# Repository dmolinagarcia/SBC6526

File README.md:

# SBC6526

SBC6526 is a single board computer built around A 65c02 CPU. It has been designed with a very specific purpose, that has defined both its name and its specs. I've been working for some time already on a MOS6526 (The famous CIA used in Commodore Computers) replica using 74xx logic series ICs. Testing was done on a real C64, but soon this prove to be a very limiting factor. So I begin working on a small SBC, designed entirely around the 6526, that should allow me to run as many tests, with no limitations at all.

The initial set of requisites was

* Continuosly variable clock, from 1MHz to as far as possible, in order to push my replica to its limits
* Clock Frequency Display. Useful, and should look very cool.
* No input at all. Program the ROM (more on this later) and just run a suite of tests for the 6526.
* Basic output.. Something like a 20x4 Character LCD will do.
* Easy, quick, and on board ROM programming. I will be modifiying the code continuosly, so this is very important.
* Include a 6522. Why not!? It can also be useful for the tests
* Include a socket for a 6526. Compatibility with old NMOS 6526 is not needed, although it would be nice.
* Allow testing of all 6526 pins. Ports, serial, /FLAG interrupt, etc
* Independent reset for 6526.

SBCv1 came to life, fulfilling this requirements. Howeever, after using it for some time, it show some weakness. SBCv1 has a 6522 and a 6526. A 4x40 LCD is used as display, driven by the 6526. This causes the display to blank when running some tests, and sometimes, crashed the LCD into an unrecoverable state, that requires a complete power down. This along some layout issues, forced the next revision. 

## Memory Map

0000 - 7FFF RAM
8000 - 87FF I/O BANK 0 - FREE
8800 - 8FFF I/O BANK 1 - CIA1
9000 - 97FF I/O BANK 2 - VIA
9800 - 9FFF I/O BANK 3 - CIAEXT
A000 - A7FF I/O BANK 4
A800 - AFFF I/O BANK 5
B000 - B7FF I/O BANK 6
B800 - BFFF I/O BANK 7
C000 - FFFF RAM

# v2
Being my first attempt at creating a SBC, v1 had many flaws. There were some pull-up resistors missing, the PCB layout was a mess, the bootstrap code was... well... unreadable to be honest. Moreover, the CAD tool I choose for v1, Eagle Cad, has a nasty licensing which is pulling away many users. I decided to make the transition to KiCAD for the v2. It's still a work in progress, and completely untested, but feel free to take a look if you like.

SBCv2 adds a second 6526. There's a 40 pin DIP socket that accepts both a MOS6526 or any modern replacement. Second 6526 connects over a 40 pin IDC that matches the 74HCT6526 interface. The LCD is now driven by the 6522, so both 6526 are 100% usable for testing. 

On SBCv1, TOD in the 6526 was used to determine clock speed. Now, a 60hz signal generated by the arduino goes into the 6522 for this purpose. SBC6526 can now startup and run with no 6526 connected at all. 

## BootStrap

The SBC6526 has no ROM. RAM exists between 0000-7FFF and C000-FFFF. As you know, the 6502 CPU needs the startup vectors to be present in the last segment of memory so, how does the SBC6526 boot?

An Arduino NANO handles the startup sequence. On startup, it brings BE low, disconnecting the 6502 from the address and data busses, and the R/W line. This also enables a pair of 8bit shift registers that handle from now on the address bus.

The RAM IC has 2 enable inputs. One is controled via the SBC Address Decoding logic, the other, directly by the ARDUINO. During BootStraping, RAMCE pulses with PHI2 (independent from the arduino) and the Arduino pulses CE line. This is a bit unorthodox and may cause some failures to write, if the arduino pulse happens when PHI2 is  high. This is handled by trying several times to write.

When the ROM image is written, BE is released, and the 6502 is resetted by the Arduino itself.

## KiCAD

Full schematic and PCB. The migration from EagleCAD to KiCAD has not been easy, as I was very much used to EagleCad. But the change as been worth the effort. 

## Firmware

With little architectural changes from v1, original firmware will need just some minor changes. Most important one, LCD screen is now driven by the 6522 instead of the 6526. Also, the internal clock measurement has to be done also with the 6522. Memory map will be the same, with just a second CIA added into an empty IO Slot.

## RamFlasher

Java code to upload memory image to SBC

## Changelog

### Unreleased

* Nothing

### v2.0.2 12-01-2022

* Minor fixes to routing
* Right VCC hole was slightly offset. Fixed
* Removed /CE from arduino to RAM. As RAMCE pulses with PHI, it's not necessary, and we leave /CE tied to GND.
* Fixed RAM footprint, as it was too wide. Improved routing.
* Added current limiting resistor to LCD Contrast
* Bootstrap and Firmware published. Not completed, but working.

### v2.0.1 29-12-2021

* Fixed a bug on LCD frequency meter footprint. Top row pads were reversed
* First draft of firmware, only for LOGISIM version
* Initial draft of bootstrap loader. Still not working.

### v2.0.0 10-19-2021

* First v2 release
* First PCB run

### v1.0.0 xx-xx-2020

* First and last v1 release
* It works, which is enough.

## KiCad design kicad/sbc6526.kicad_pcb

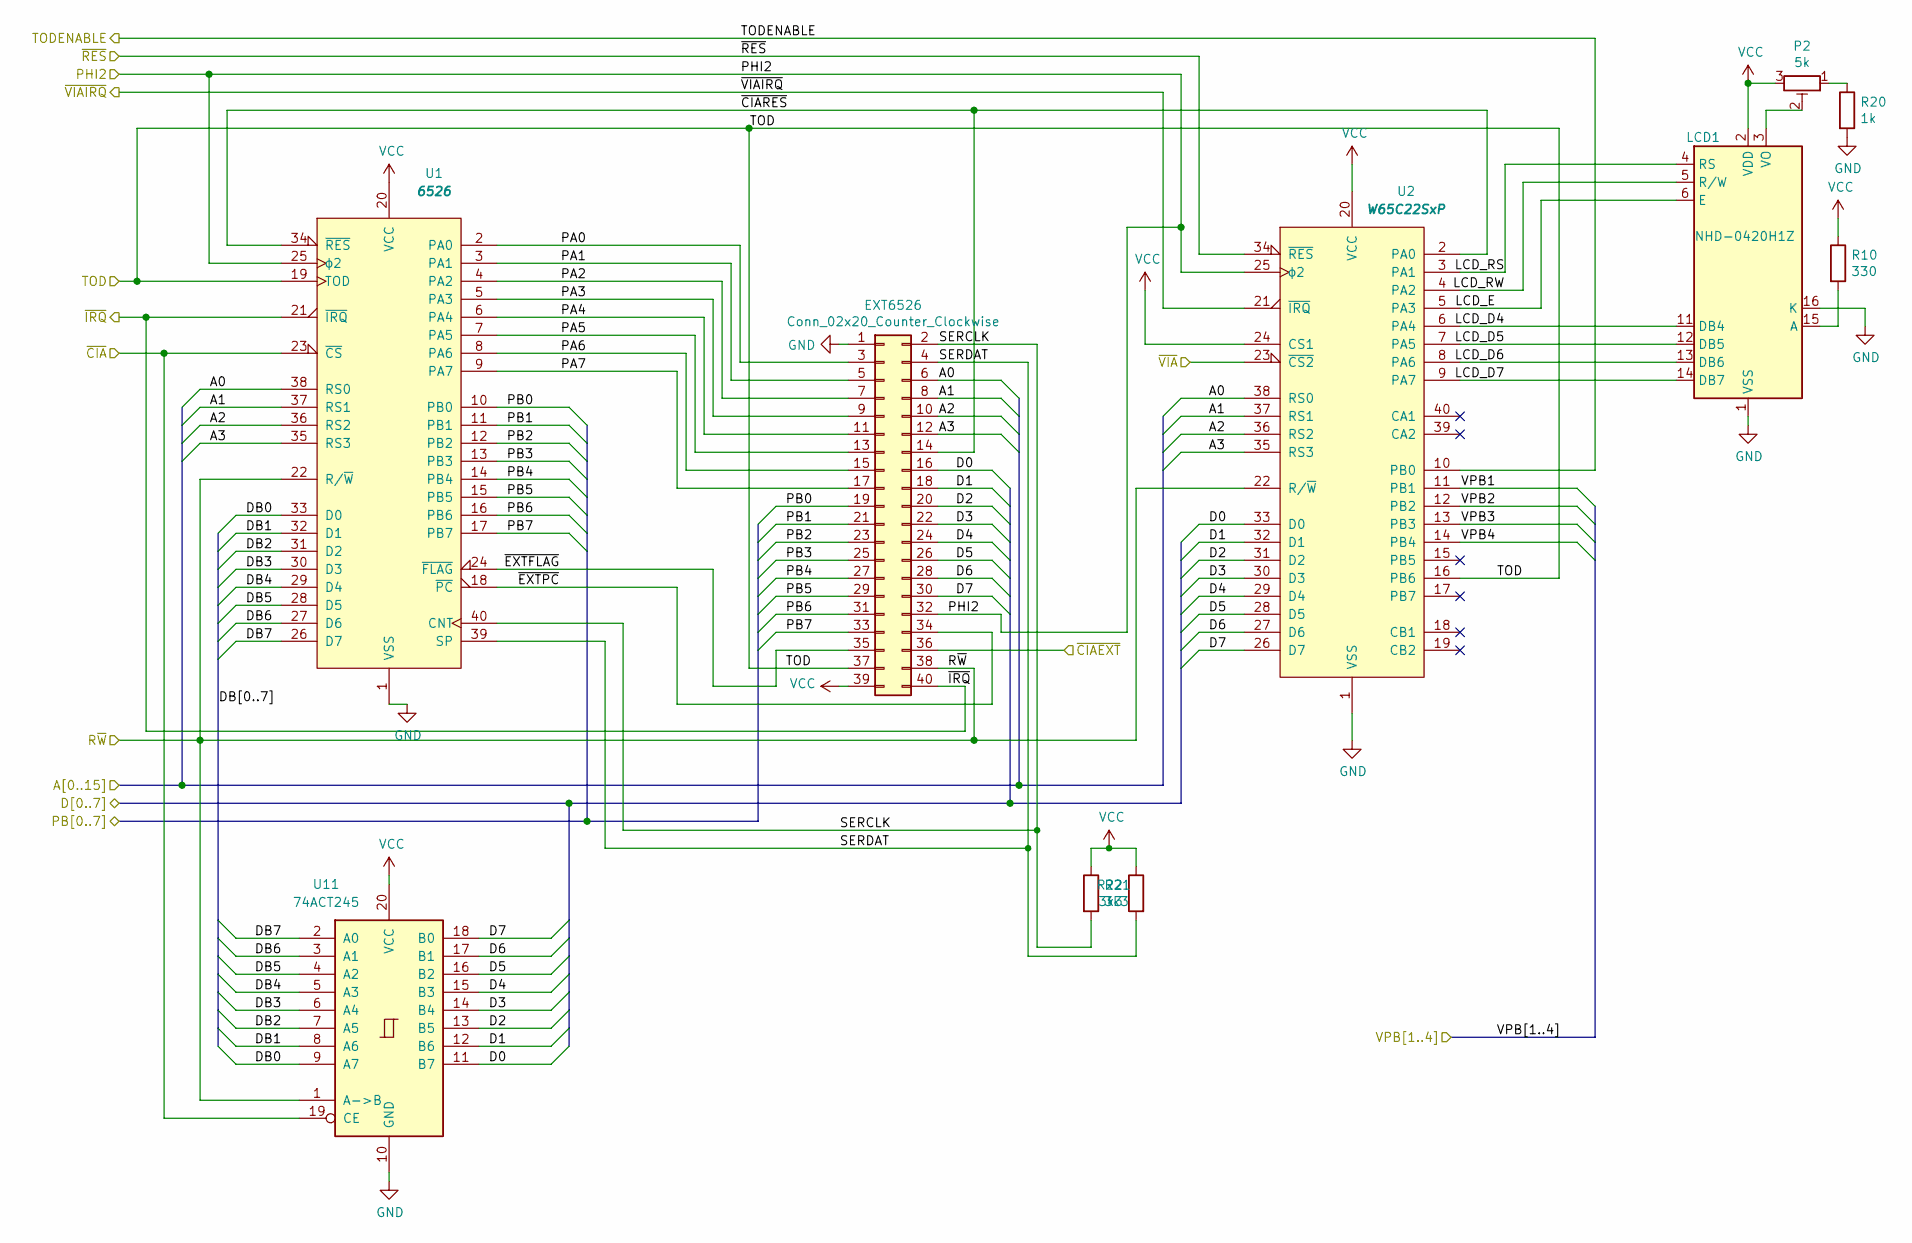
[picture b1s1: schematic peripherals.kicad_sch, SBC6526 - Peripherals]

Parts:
EXT6526: Conn_02x20_Counter_Clockwise; PinHeader_2x20_P2.54mm_Vertical
LCD1: NHD-0420H1Z; HD44780_4x20
P2: 5k; Potentiometer_Bourns_3296W_Vertical
R10: 330; R_0805_2012Metric_Pad1.20x1.40mm_HandSolder
R20: 1k; R_0805_2012Metric_Pad1.20x1.40mm_HandSolder
R21, R22: 3k3; R_0805_2012Metric_Pad1.20x1.40mm_HandSolder
U1: 6526; DIP-40_W15.24mm
U2: W65C22SxP; DIP-40_W15.24mm
U11: 74ACT245; DIP-20_W7.62mm

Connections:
/A0: EXT6526.6, U1.38 (RS0), U2.38 (RS0); also elsewhere on the board
/A1: EXT6526.8, U1.37 (RS1), U2.37 (RS1); also elsewhere on the board
/A2: EXT6526.10, U1.36 (RS2), U2.36 (RS2); also elsewhere on the board
/A3: EXT6526.12, U1.35 (RS3), U2.35 (RS3); also elsewhere on the board
/D0: EXT6526.16, U2.33 (D0), U11.11 (B7); also elsewhere on the board
/D1: EXT6526.18, U2.32 (D1), U11.12 (B6); also elsewhere on the board
/D2: EXT6526.20, U2.31 (D2), U11.13 (B5); also elsewhere on the board
/D3: EXT6526.22, U2.30 (D3), U11.14 (B4); also elsewhere on the board
/D4: EXT6526.24, U2.29 (D4), U11.15 (B3); also elsewhere on the board
/D5: EXT6526.26, U2.28 (D5), U11.16 (B2); also elsewhere on the board
/D6: EXT6526.28, U2.27 (D6), U11.17 (B1); also elsewhere on the board
/D7: EXT6526.30, U2.26 (D7), U11.18 (B0); also elsewhere on the board
/PHI2: EXT6526.32, U1.25 (ϕ2), U2.25 (ϕ2); also elsewhere on the board
/R~W: EXT6526.38, U1.22 (R/~W), U2.22 (R/~W), U11.1 (A->B); also elsewhere on the board
/TOD: EXT6526.37, U1.19 (TOD), U2.16 (PB6); also elsewhere on the board
/TODENABLE: U2.10 (PB0); also elsewhere on the board
/io/PB0: EXT6526.19, U1.10 (PB0); also elsewhere on the board
/io/PB1: EXT6526.21, U1.11 (PB1); also elsewhere on the board
/io/PB2: EXT6526.23, U1.12 (PB2); also elsewhere on the board
/io/PB3: EXT6526.25, U1.13 (PB3); also elsewhere on the board
/io/PB4: EXT6526.27, U1.14 (PB4); also elsewhere on the board
/io/PB5: EXT6526.29, U1.15 (PB5); also elsewhere on the board
/io/PB6: EXT6526.31, U1.16 (PB6); also elsewhere on the board
/io/PB7: EXT6526.33, U1.17 (PB7); also elsewhere on the board
/memory/~CIAEXT: EXT6526.36; also elsewhere on the board
/memory/~CIA: U1.23 (~CS), U11.19 (CE); also elsewhere on the board
/memory/~VIA: U2.23 (~CS2); also elsewhere on the board
/peripherals/DB0: U1.33 (D0), U11.9 (A7)
/peripherals/DB1: U1.32 (D1), U11.8 (A6)
/peripherals/DB2: U1.31 (D2), U11.7 (A5)
/peripherals/DB3: U1.30 (D3), U11.6 (A4)
/peripherals/DB4: U1.29 (D4), U11.5 (A3)
/peripherals/DB5: U1.28 (D5), U11.4 (A2)
/peripherals/DB6: U1.27 (D6), U11.3 (A1)
/peripherals/DB7: U1.26 (D7), U11.2 (A0)
/peripherals/LCD_D4: LCD1.11 (DB4), U2.6 (PA4)
/peripherals/LCD_D5: LCD1.12 (DB5), U2.7 (PA5)
/peripherals/LCD_D6: LCD1.13 (DB6), U2.8 (PA6)
/peripherals/LCD_D7: LCD1.14 (DB7), U2.9 (PA7)
/peripherals/LCD_E: LCD1.6 (E), U2.5 (PA3)
/peripherals/LCD_RS: LCD1.4 (RS), U2.3 (PA1)
/peripherals/LCD_RW: LCD1.5 (R/W), U2.4 (PA2)
/peripherals/PA0: EXT6526.3, U1.2 (PA0)
/peripherals/PA1: EXT6526.5, U1.3 (PA1)
/peripherals/PA2: EXT6526.7, U1.4 (PA2)
/peripherals/PA3: EXT6526.9, U1.5 (PA3)
/peripherals/PA4: EXT6526.11, U1.6 (PA4)
/peripherals/PA5: EXT6526.13, U1.7 (PA5)
/peripherals/PA6: EXT6526.15, U1.8 (PA6)
/peripherals/PA7: EXT6526.17, U1.9 (PA7)
/peripherals/SERCLK: EXT6526.2, R21.2, U1.40 (CNT)
/peripherals/SERDAT: EXT6526.4, R22.2, U1.39 (SP)
/peripherals/VPB1: U2.11 (PB1); also elsewhere on the board
/peripherals/VPB2: U2.12 (PB2); also elsewhere on the board
/peripherals/VPB3: U2.13 (PB3); also elsewhere on the board
/peripherals/VPB4: U2.14 (PB4); also elsewhere on the board
/peripherals/~CIARES: EXT6526.14, U1.34 (~RES), U2.2 (PA0)
/peripherals/~EXTFLAG: EXT6526.35, U1.24 (~FLAG)
/peripherals/~EXTPC: EXT6526.34, U1.18 (~PC)
/~IRQ: EXT6526.40, U1.21 (~IRQ); also elsewhere on the board
/~RES: U2.34 (~RES); also elsewhere on the board
/~VIAIRQ: U2.21 (~IRQ); also elsewhere on the board
GND: EXT6526.1, LCD1.1 (VSS), LCD1.16 (K), R20.2, U1.1 (VSS), U2.1 (VSS), U11.10 (GND); also elsewhere on the board
unnamed: LCD1.3 (VO), P2.2
unnamed: LCD1.15 (A), R10.2
unnamed: P2.1, R20.1
VCC: EXT6526.39, LCD1.2 (VDD), P2.3, R10.1, R21.1, R22.1, U1.20 (VCC), U2.20 (VCC), U2.24 (CS1), U11.20 (VCC); also elsewhere on the board

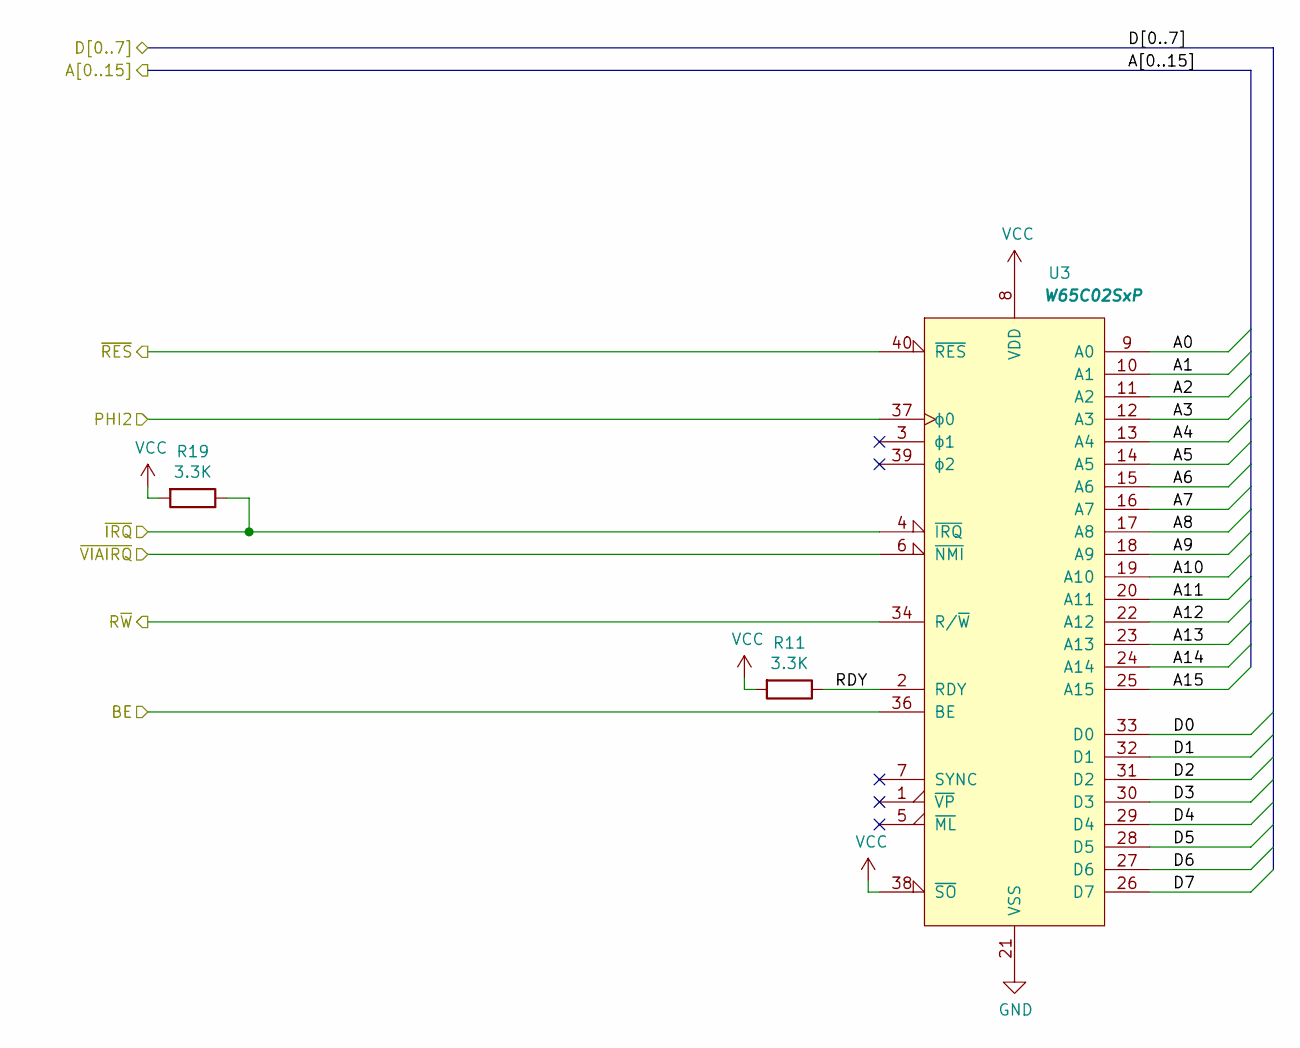
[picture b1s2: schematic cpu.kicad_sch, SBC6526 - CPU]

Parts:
R11, R19: 3.3K; R_0805_2012Metric_Pad1.20x1.40mm_HandSolder
U3: W65C02SxP; DIP-40_W15.24mm

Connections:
/A0: U3.9 (A0); also elsewhere on the board
/A1: U3.10 (A1); also elsewhere on the board
/A2: U3.11 (A2); also elsewhere on the board
/A3: U3.12 (A3); also elsewhere on the board
/A4: U3.13 (A4); also elsewhere on the board
/A5: U3.14 (A5); also elsewhere on the board
/A6: U3.15 (A6); also elsewhere on the board
/A7: U3.16 (A7); also elsewhere on the board
/A8: U3.17 (A8); also elsewhere on the board
/A9: U3.18 (A9); also elsewhere on the board
/A10: U3.19 (A10); also elsewhere on the board
/A11: U3.20 (A11); also elsewhere on the board
/A12: U3.22 (A12); also elsewhere on the board
/A13: U3.23 (A13); also elsewhere on the board
/A14: U3.24 (A14); also elsewhere on the board
/A15: U3.25 (A15); also elsewhere on the board
/D0: U3.33 (D0); also elsewhere on the board
/D1: U3.32 (D1); also elsewhere on the board
/D2: U3.31 (D2); also elsewhere on the board
/D3: U3.30 (D3); also elsewhere on the board
/D4: U3.29 (D4); also elsewhere on the board
/D5: U3.28 (D5); also elsewhere on the board
/D6: U3.27 (D6); also elsewhere on the board
/D7: U3.26 (D7); also elsewhere on the board
/PHI2: U3.37 (ϕ0); also elsewhere on the board
/R~W: U3.34 (R/~W); also elsewhere on the board
/bootstrap/BE: U3.36 (BE); also elsewhere on the board
/cpu/RDY: R11.1, U3.2 (RDY)
/~IRQ: R19.1, U3.4 (~IRQ); also elsewhere on the board
/~RES: U3.40 (~RES); also elsewhere on the board
/~VIAIRQ: U3.6 (~NMI); also elsewhere on the board
GND: U3.21 (VSS); also elsewhere on the board
VCC: R11.2, R19.2, U3.8 (VDD), U3.38 (~SO); also elsewhere on the board

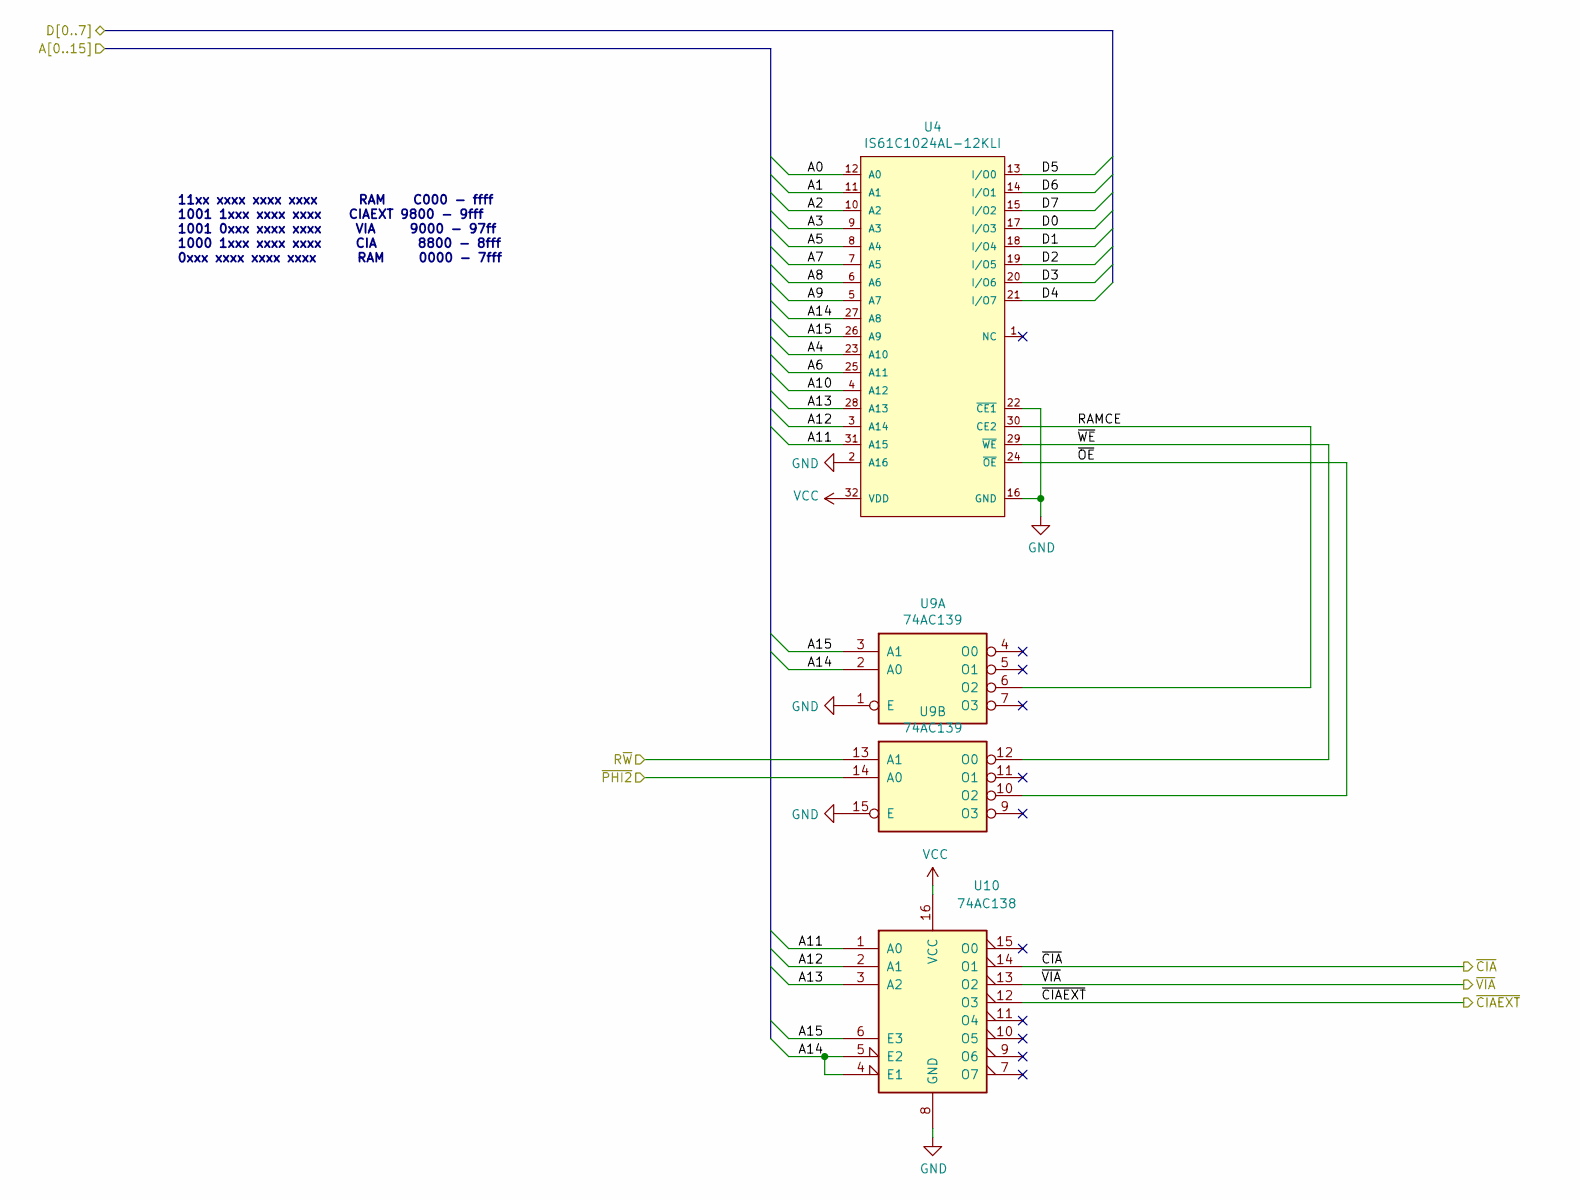
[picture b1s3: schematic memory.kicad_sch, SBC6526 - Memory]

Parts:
U4: IS61C1024AL-12KLI; SOJ-32_10.16x21.08mm_P1.27mm
U9: 74AC139; SOIC-16_3.9x9.9mm_P1.27mm
U10: 74AC138; SOIC-16_3.9x9.9mm_P1.27mm

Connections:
/A0: U4.12 (A0); also elsewhere on the board
/A1: U4.11 (A1); also elsewhere on the board
/A2: U4.10 (A2); also elsewhere on the board
/A3: U4.9 (A3); also elsewhere on the board
/A4: U4.23 (A10); also elsewhere on the board
/A5: U4.8 (A4); also elsewhere on the board
/A6: U4.25 (A11); also elsewhere on the board
/A7: U4.7 (A5); also elsewhere on the board
/A8: U4.6 (A6); also elsewhere on the board
/A9: U4.5 (A7); also elsewhere on the board
/A10: U4.4 (A12); also elsewhere on the board
/A11: U4.31 (A15), U10.1 (A0); also elsewhere on the board
/A12: U4.3 (A14), U10.2 (A1); also elsewhere on the board
/A13: U4.28 (A13), U10.3 (A2); also elsewhere on the board
/A14: U4.27 (A8), U9.2 (A0), U10.4 (E1), U10.5 (E2); also elsewhere on the board
/A15: U4.26 (A9), U9.3 (A1), U10.6 (E3); also elsewhere on the board
/D0: U4.17 (I/O3); also elsewhere on the board
/D1: U4.18 (I/O4); also elsewhere on the board
/D2: U4.19 (I/O5); also elsewhere on the board
/D3: U4.20 (I/O6); also elsewhere on the board
/D4: U4.21 (I/O7); also elsewhere on the board
/D5: U4.13 (I/O0); also elsewhere on the board
/D6: U4.14 (I/O1); also elsewhere on the board
/D7: U4.15 (I/O2); also elsewhere on the board
/R~W: U9.13 (A1); also elsewhere on the board
/clock/~PHI2: U9.14 (A0); also elsewhere on the board
/memory/RAMCE: U4.30 (CE2), U9.6 (O2)
/memory/~CIAEXT: U10.12 (O3); also elsewhere on the board
/memory/~CIA: U10.14 (O1); also elsewhere on the board
/memory/~OE: U4.24 (~OE), U9.10 (O2)
/memory/~VIA: U10.13 (O2); also elsewhere on the board
/memory/~WE: U4.29 (~WE), U9.12 (O0)
GND: U4.2 (A16), U4.16 (GND), U4.22 (~CE1), U9.1 (E), U9.15 (E), U10.8 (GND); also elsewhere on the board
VCC: U4.32 (VDD), U10.16 (VCC); also elsewhere on the board

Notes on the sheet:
11xx xxxx xxxx xxxx RAM C000 - ffff 1001 1xxx xxxx xxxx CIAEXT 9800 - 9fff 1001 0xxx xxxx xxxx VIA 9000 - 97ff 1000 1xxx xxxx xxxx CIA 8800 - 8fff 0xxx xxxx xxxx xxxx RAM 0000 - 7fff

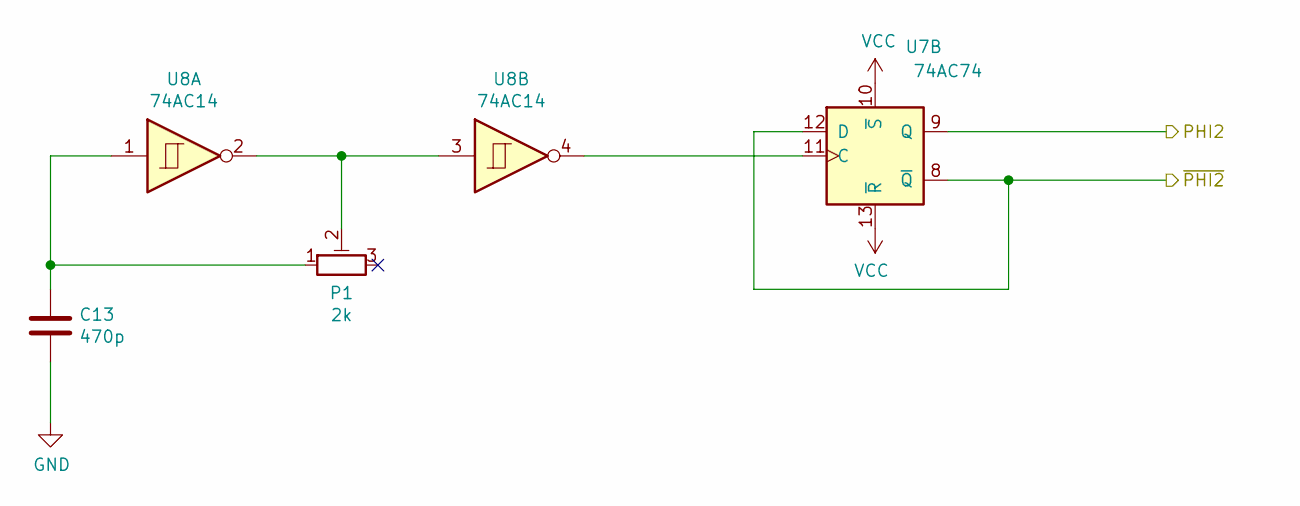
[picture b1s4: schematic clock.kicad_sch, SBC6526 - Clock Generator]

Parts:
C13: 470p; C_0805_2012Metric_Pad1.18x1.45mm_HandSolder
P1: 2k; Potentiometer_Bourns_3296W_Vertical
U7: 74AC74; SOIC-14_3.9x8.7mm_P1.27mm
U8: 74AC14; SOIC-14_3.9x8.7mm_P1.27mm

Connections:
/PHI2: U7.9 (Q); also elsewhere on the board
/clock/~PHI2: U7.8 (~Q), U7.12 (D); also elsewhere on the board
GND: C13.2; also elsewhere on the board
unnamed: C13.1, P1.1, U8.1
unnamed: P1.2, U8.2, U8.3
unnamed: U7.11 (C), U8.4
VCC: U7.10 (~S), U7.13 (~R); also elsewhere on the board

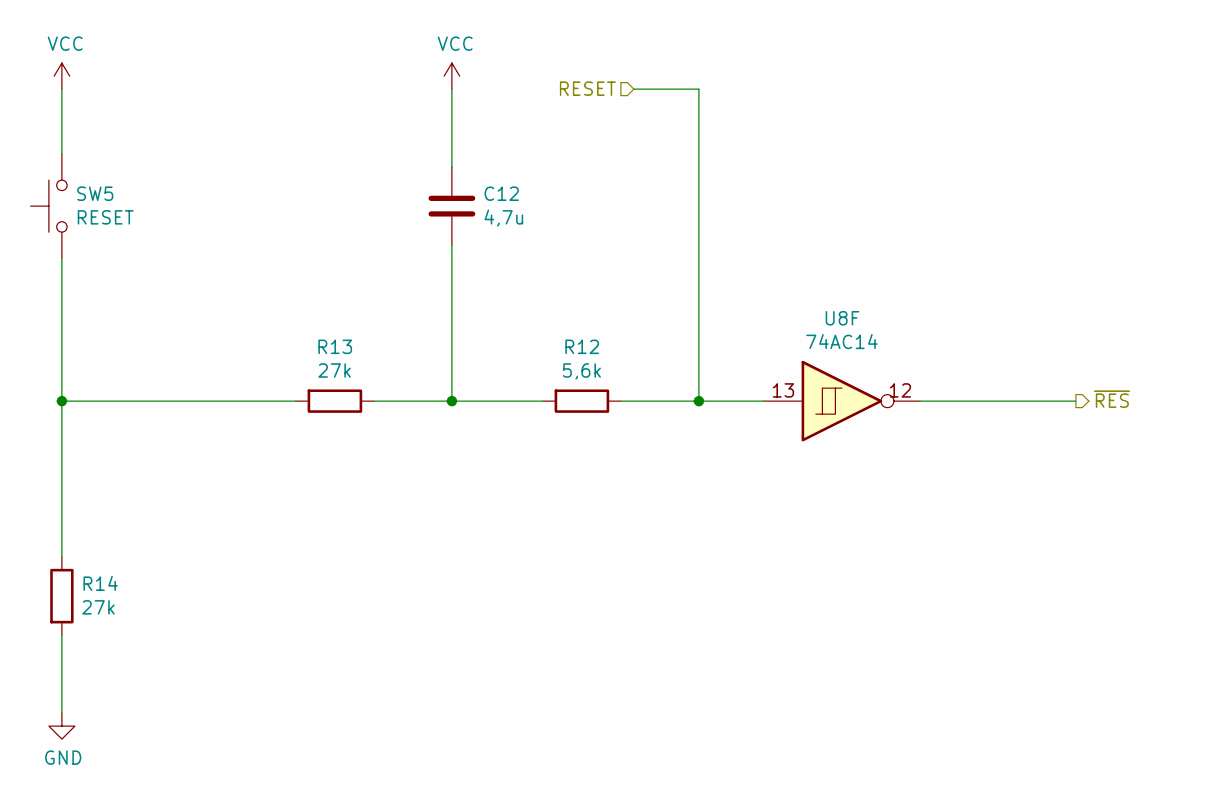
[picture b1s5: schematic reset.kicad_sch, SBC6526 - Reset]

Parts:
C12: 4,7u; C_0805_2012Metric_Pad1.18x1.45mm_HandSolder
R12: 5,6k; R_0805_2012Metric_Pad1.20x1.40mm_HandSolder
R13, R14: 27k; R_0805_2012Metric_Pad1.20x1.40mm_HandSolder
SW5: RESET; SW_TH_Tactile_Omron_B3F-10xx
U8: 74AC14; SOIC-14_3.9x8.7mm_P1.27mm

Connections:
/bootstrap/RESET: R12.1, U8.13; also elsewhere on the board
/~RES: U8.12; also elsewhere on the board
GND: R14.2; also elsewhere on the board
unnamed: C12.2, R12.2, R13.1
unnamed: R13.2, R14.1, SW5.1 (A), SW5.2 (A)
VCC: C12.1, SW5.3 (B), SW5.4 (B); also elsewhere on the board

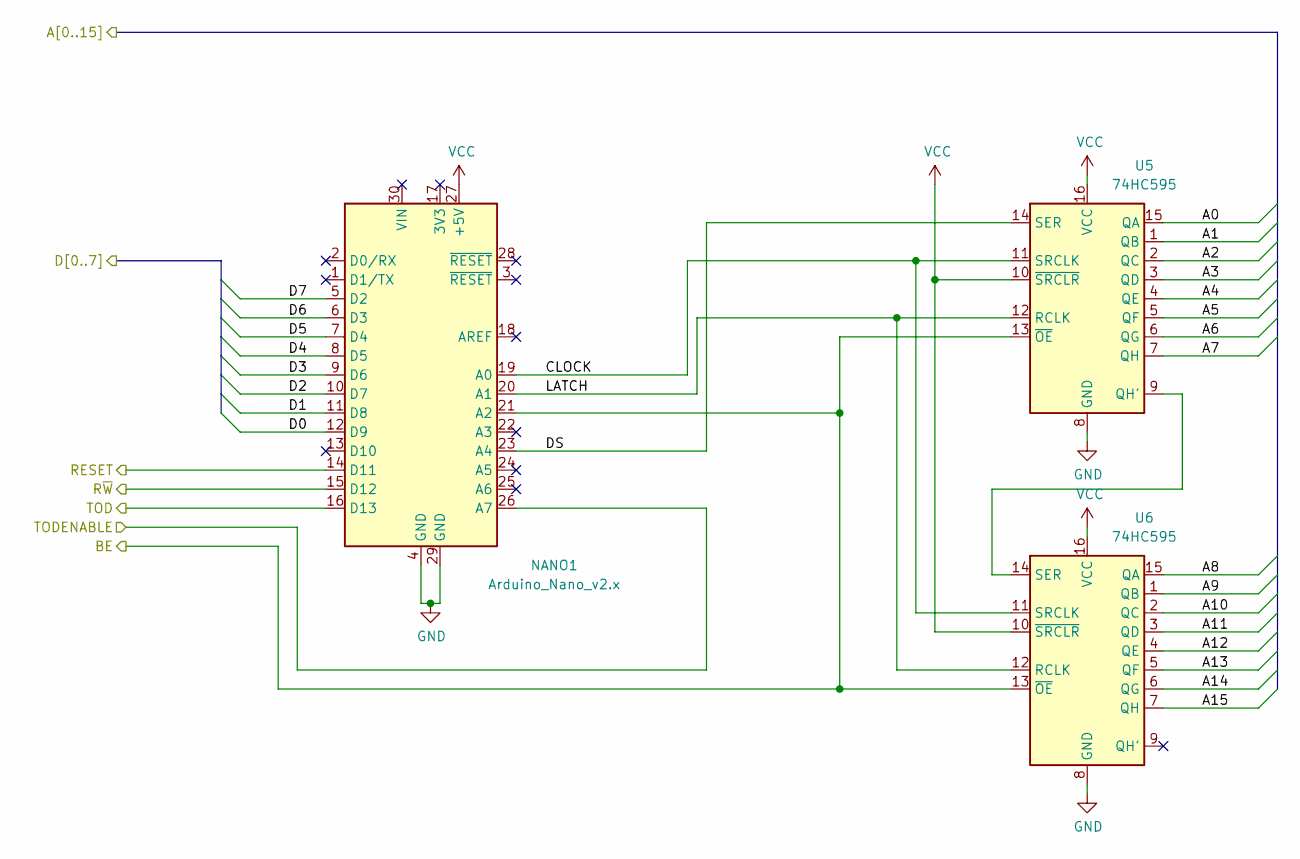
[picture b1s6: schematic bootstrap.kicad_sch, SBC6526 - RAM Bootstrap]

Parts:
NANO1: Arduino_Nano_v2.x; Arduino_Nano
U5, U6: 74HC595; SOIC-16_3.9x9.9mm_P1.27mm

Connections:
/A0: U5.15 (QA); also elsewhere on the board
/A1: U5.1 (QB); also elsewhere on the board
/A2: U5.2 (QC); also elsewhere on the board
/A3: U5.3 (QD); also elsewhere on the board
/A4: U5.4 (QE); also elsewhere on the board
/A5: U5.5 (QF); also elsewhere on the board
/A6: U5.6 (QG); also elsewhere on the board
/A7: U5.7 (QH); also elsewhere on the board
/A8: U6.15 (QA); also elsewhere on the board
/A9: U6.1 (QB); also elsewhere on the board
/A10: U6.2 (QC); also elsewhere on the board
/A11: U6.3 (QD); also elsewhere on the board
/A12: U6.4 (QE); also elsewhere on the board
/A13: U6.5 (QF); also elsewhere on the board
/A14: U6.6 (QG); also elsewhere on the board
/A15: U6.7 (QH); also elsewhere on the board
/D0: NANO1.12 (D9); also elsewhere on the board
/D1: NANO1.11 (D8); also elsewhere on the board
/D2: NANO1.10 (D7); also elsewhere on the board
/D3: NANO1.9 (D6); also elsewhere on the board
/D4: NANO1.8 (D5); also elsewhere on the board
/D5: NANO1.7 (D4); also elsewhere on the board
/D6: NANO1.6 (D3); also elsewhere on the board
/D7: NANO1.5 (D2); also elsewhere on the board
/R~W: NANO1.15 (D12); also elsewhere on the board
/TOD: NANO1.16 (D13); also elsewhere on the board
/TODENABLE: NANO1.26 (A7); also elsewhere on the board
/bootstrap/BE: NANO1.21 (A2), U5.13 (~OE), U6.13 (~OE); also elsewhere on the board
/bootstrap/CLOCK: NANO1.19 (A0), U5.11 (SRCLK), U6.11 (SRCLK)
/bootstrap/DS: NANO1.23 (A4), U5.14 (SER)
/bootstrap/LATCH: NANO1.20 (A1), U5.12 (RCLK), U6.12 (RCLK)
/bootstrap/RESET: NANO1.14 (D11); also elsewhere on the board
GND: NANO1.4 (GND), NANO1.29 (GND), U5.8 (GND), U6.8 (GND); also elsewhere on the board
unnamed: U5.9 (QH'), U6.14 (SER)
VCC: NANO1.27 (+5V), U5.10 (~SRCLR), U5.16 (VCC), U6.10 (~SRCLR), U6.16 (VCC); also elsewhere on the board

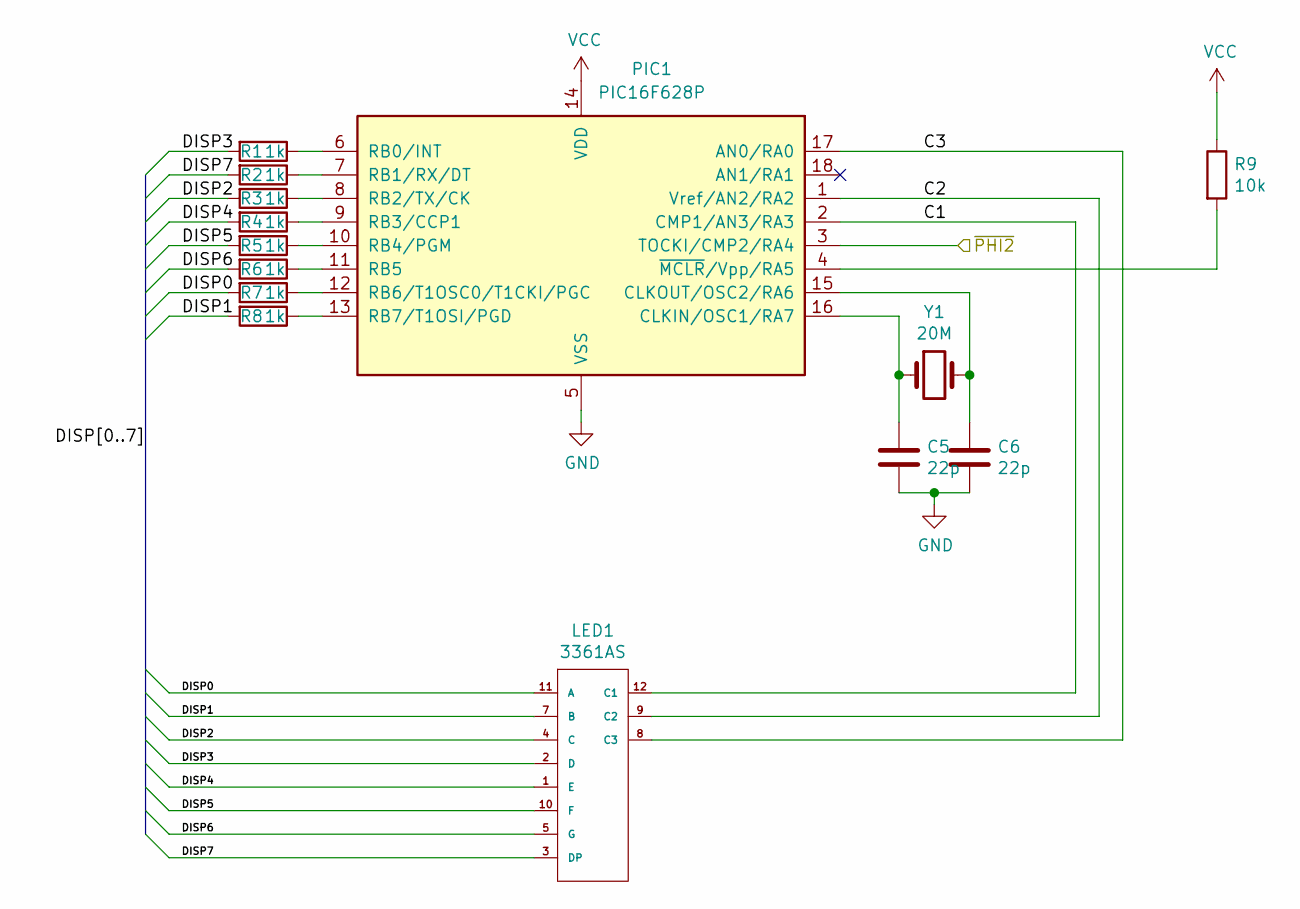
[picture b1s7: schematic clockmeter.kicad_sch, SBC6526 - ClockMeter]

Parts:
C5, C6: 22p; C_0805_2012Metric_Pad1.18x1.45mm_HandSolder
LED1: 3361AS; 3digit-7segment3361
PIC1: PIC16F628P; DIP-18_W7.62mm
R1, R2, R3, R4, R5, R6, R7, R8: 1k; R_0805_2012Metric_Pad1.20x1.40mm_HandSolder
R9: 10k; R_0805_2012Metric_Pad1.20x1.40mm_HandSolder
Y1: 20M; R_Axial_DIN0204_L3.6mm_D1.6mm_P5.08mm_Horizontal

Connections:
/clock/~PHI2: PIC1.3 (TOCKI/CMP2/RA4); also elsewhere on the board
/clockmeter/C1: LED1.12 (C1), PIC1.2 (CMP1/AN3/RA3)
/clockmeter/C2: LED1.9 (C2), PIC1.1 (Vref/AN2/RA2)
/clockmeter/C3: LED1.8 (C3), PIC1.17 (AN0/RA0)
/clockmeter/DISP0: LED1.11 (A), R7.2
/clockmeter/DISP1: LED1.7 (B), R8.2
/clockmeter/DISP2: LED1.4 (C), R3.2
/clockmeter/DISP3: LED1.2 (D), R1.2
/clockmeter/DISP4: LED1.1 (E), R4.2
/clockmeter/DISP5: LED1.10 (F), R5.2
/clockmeter/DISP6: LED1.5 (G), R6.2
/clockmeter/DISP7: LED1.3 (DP), R2.2
GND: C5.2, C6.2, PIC1.5 (VSS); also elsewhere on the board
unnamed: C5.1, PIC1.16 (CLKIN/OSC1/RA7), Y1.1
unnamed: C6.1, PIC1.15 (CLKOUT/OSC2/RA6), Y1.2
unnamed: PIC1.4 (~MCLR/Vpp/RA5), R9.2
unnamed: PIC1.6 (RB0/INT), R1.1
unnamed: PIC1.7 (RB1/RX/DT), R2.1
unnamed: PIC1.8 (RB2/TX/CK), R3.1
unnamed: PIC1.9 (RB3/CCP1), R4.1
unnamed: PIC1.10 (RB4/PGM), R5.1
unnamed: PIC1.11 (RB5), R6.1
unnamed: PIC1.12 (RB6/T1OSC0/T1CKI/PGC), R7.1
unnamed: PIC1.13 (RB7/T1OSI/PGD), R8.1
VCC: PIC1.14 (VDD), R9.1; also elsewhere on the board

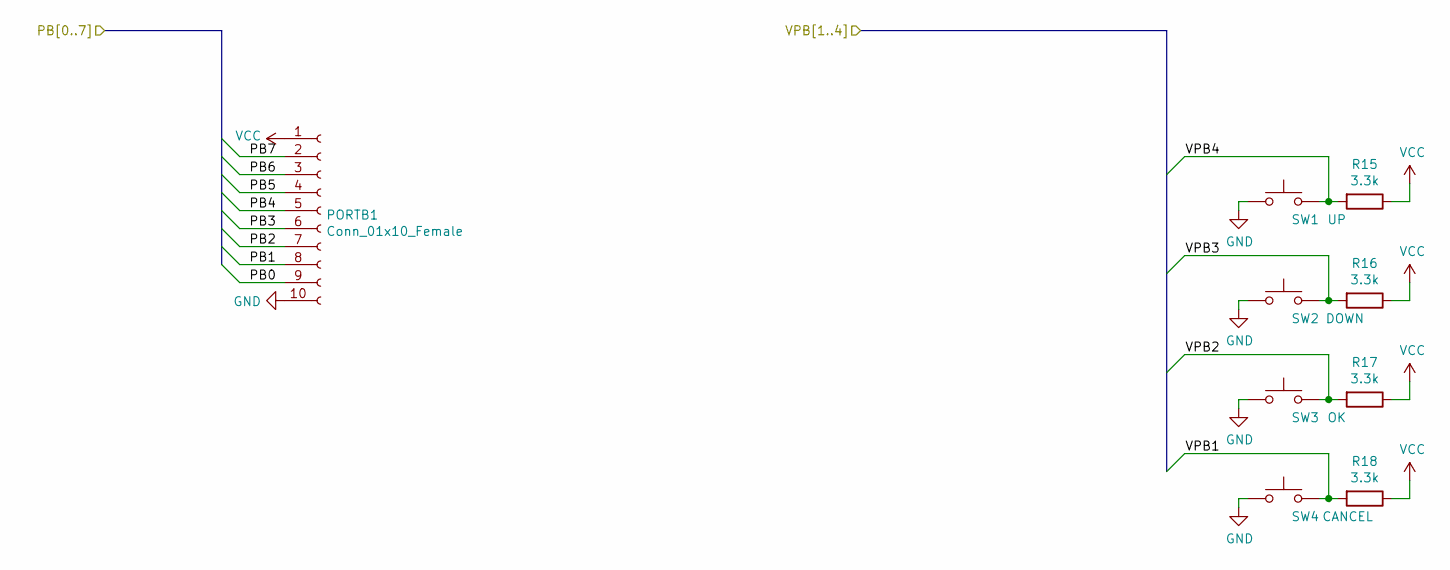
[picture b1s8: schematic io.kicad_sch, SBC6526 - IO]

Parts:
PORTB1: Conn_01x10_Female; PinSocket_2x05_P2.54mm_Vertical
R15, R16, R17, R18: 3.3k; R_0805_2012Metric_Pad1.20x1.40mm_HandSolder
SW1: UP; SW_TH_Tactile_Omron_B3F-10xx
SW2: DOWN; SW_TH_Tactile_Omron_B3F-10xx
SW3: OK; SW_TH_Tactile_Omron_B3F-10xx
SW4: CANCEL; SW_TH_Tactile_Omron_B3F-10xx

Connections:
/io/PB0: PORTB1.9; also elsewhere on the board
/io/PB1: PORTB1.8; also elsewhere on the board
/io/PB2: PORTB1.7; also elsewhere on the board
/io/PB3: PORTB1.6; also elsewhere on the board
/io/PB4: PORTB1.5; also elsewhere on the board
/io/PB5: PORTB1.4; also elsewhere on the board
/io/PB6: PORTB1.3; also elsewhere on the board
/io/PB7: PORTB1.2; also elsewhere on the board
/peripherals/VPB1: R18.2, SW4.3 (B), SW4.4 (B); also elsewhere on the board
/peripherals/VPB2: R17.2, SW3.3 (B), SW3.4 (B); also elsewhere on the board
/peripherals/VPB3: R16.2, SW2.3 (B), SW2.4 (B); also elsewhere on the board
/peripherals/VPB4: R15.2, SW1.3 (B), SW1.4 (B); also elsewhere on the board
GND: PORTB1.10, SW1.1 (A), SW1.2 (A), SW2.1 (A), SW2.2 (A), SW3.1 (A), SW3.2 (A), SW4.1 (A), SW4.2 (A); also elsewhere on the board
VCC: PORTB1.1, R15.1, R16.1, R17.1, R18.1; also elsewhere on the board

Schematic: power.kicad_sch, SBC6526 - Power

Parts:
C1, C2, C3, C4, C7, C8, C9, C10, C11: 100n; C_0805_2012Metric_Pad1.18x1.45mm_HandSolder
C14: 10u; CP_Radial_D6.3mm_P2.50mm
CEXT1: 100n; C_0805_2012Metric_Pad1.18x1.45mm_HandSolder
U7: 74AC74; SOIC-14_3.9x8.7mm_P1.27mm
U8: 74AC14; SOIC-14_3.9x8.7mm_P1.27mm
U9: 74AC139; SOIC-16_3.9x9.9mm_P1.27mm

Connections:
GND: C1.2, C2.2, C3.2, C4.2, C7.2, C8.2, C9.2, C10.2, C11.2, C14.2, CEXT1.2, U7.2 (D), U7.3 (C), U7.7 (GND), U8.5, U8.7 (GND), U8.9, U8.11, U9.8 (GND); also elsewhere on the board
VCC: C1.1, C2.1, C3.1, C4.1, C7.1, C8.1, C9.1, C10.1, C11.1, C14.1, CEXT1.1, U7.1 (~R), U7.4 (~S), U7.14 (VCC), U8.14 (VCC), U9.16 (VCC); also elsewhere on the board

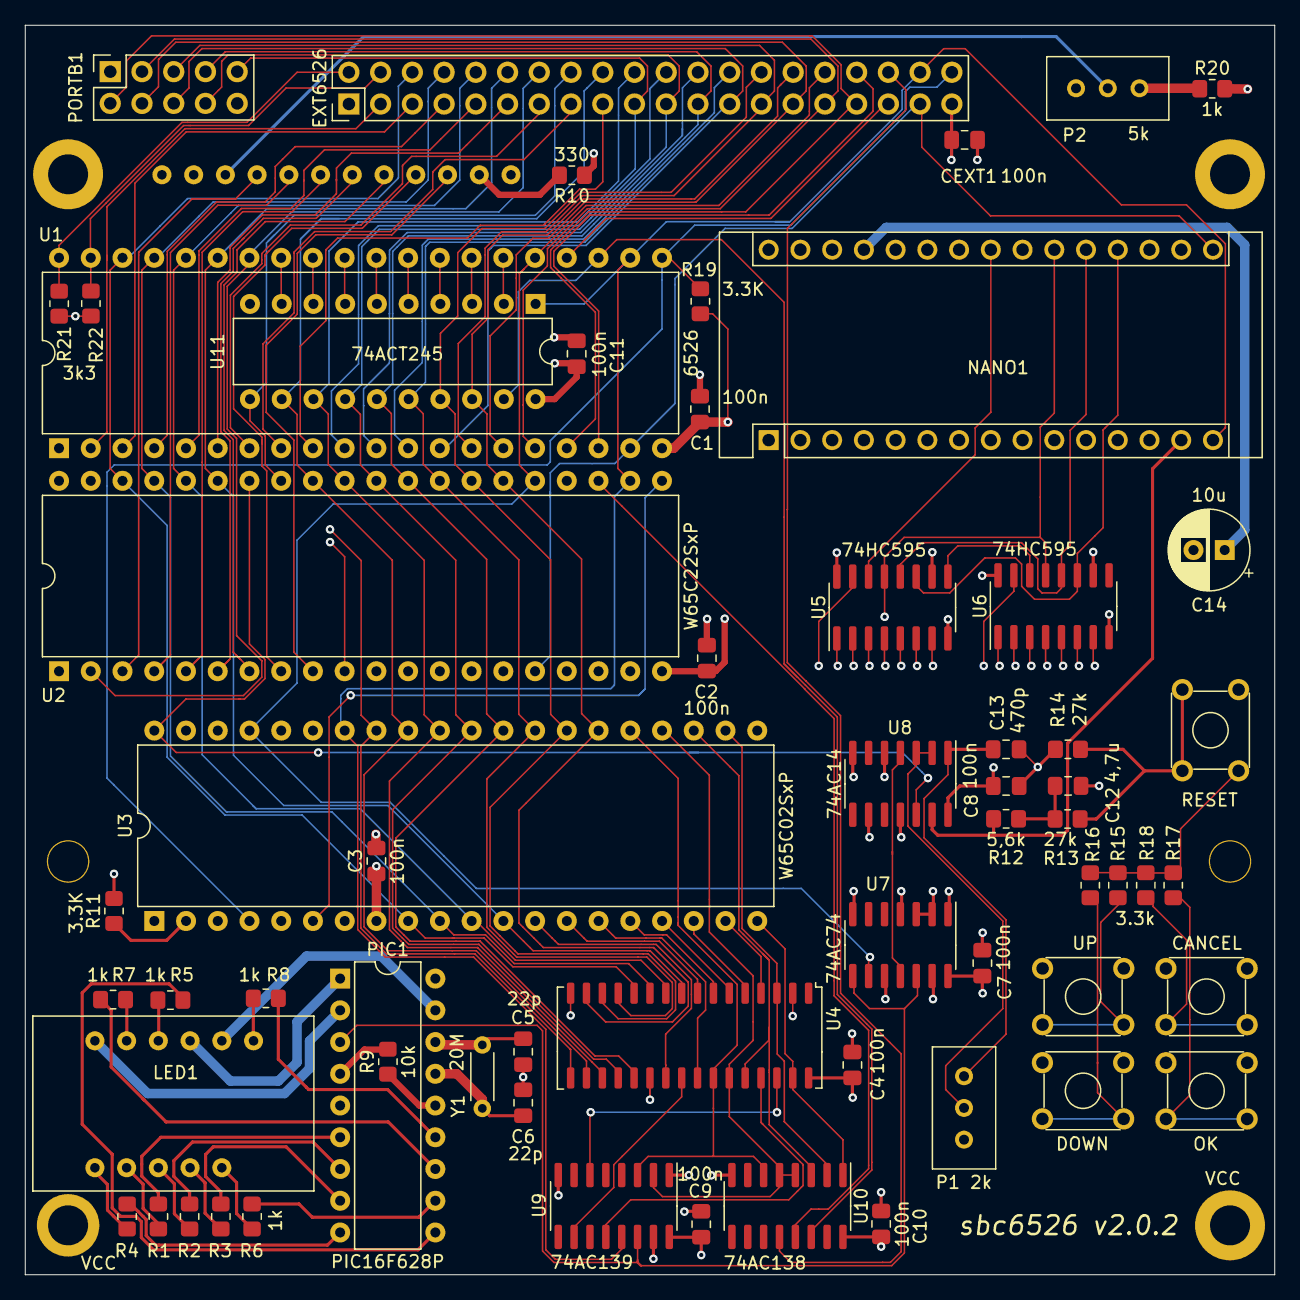
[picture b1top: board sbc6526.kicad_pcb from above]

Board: 4 copper layers, 100.0 x 100.0 mm, 64 parts (0 on the bottom side), 117 nets.

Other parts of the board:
VCC1, VCC2: VCC; MountingHole_2.2mm_M2_DIN965_Pad

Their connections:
VCC: VCC1.VCC, VCC2.VCC; also elsewhere on the board
